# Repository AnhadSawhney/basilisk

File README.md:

# basilisk
 interactive LED art

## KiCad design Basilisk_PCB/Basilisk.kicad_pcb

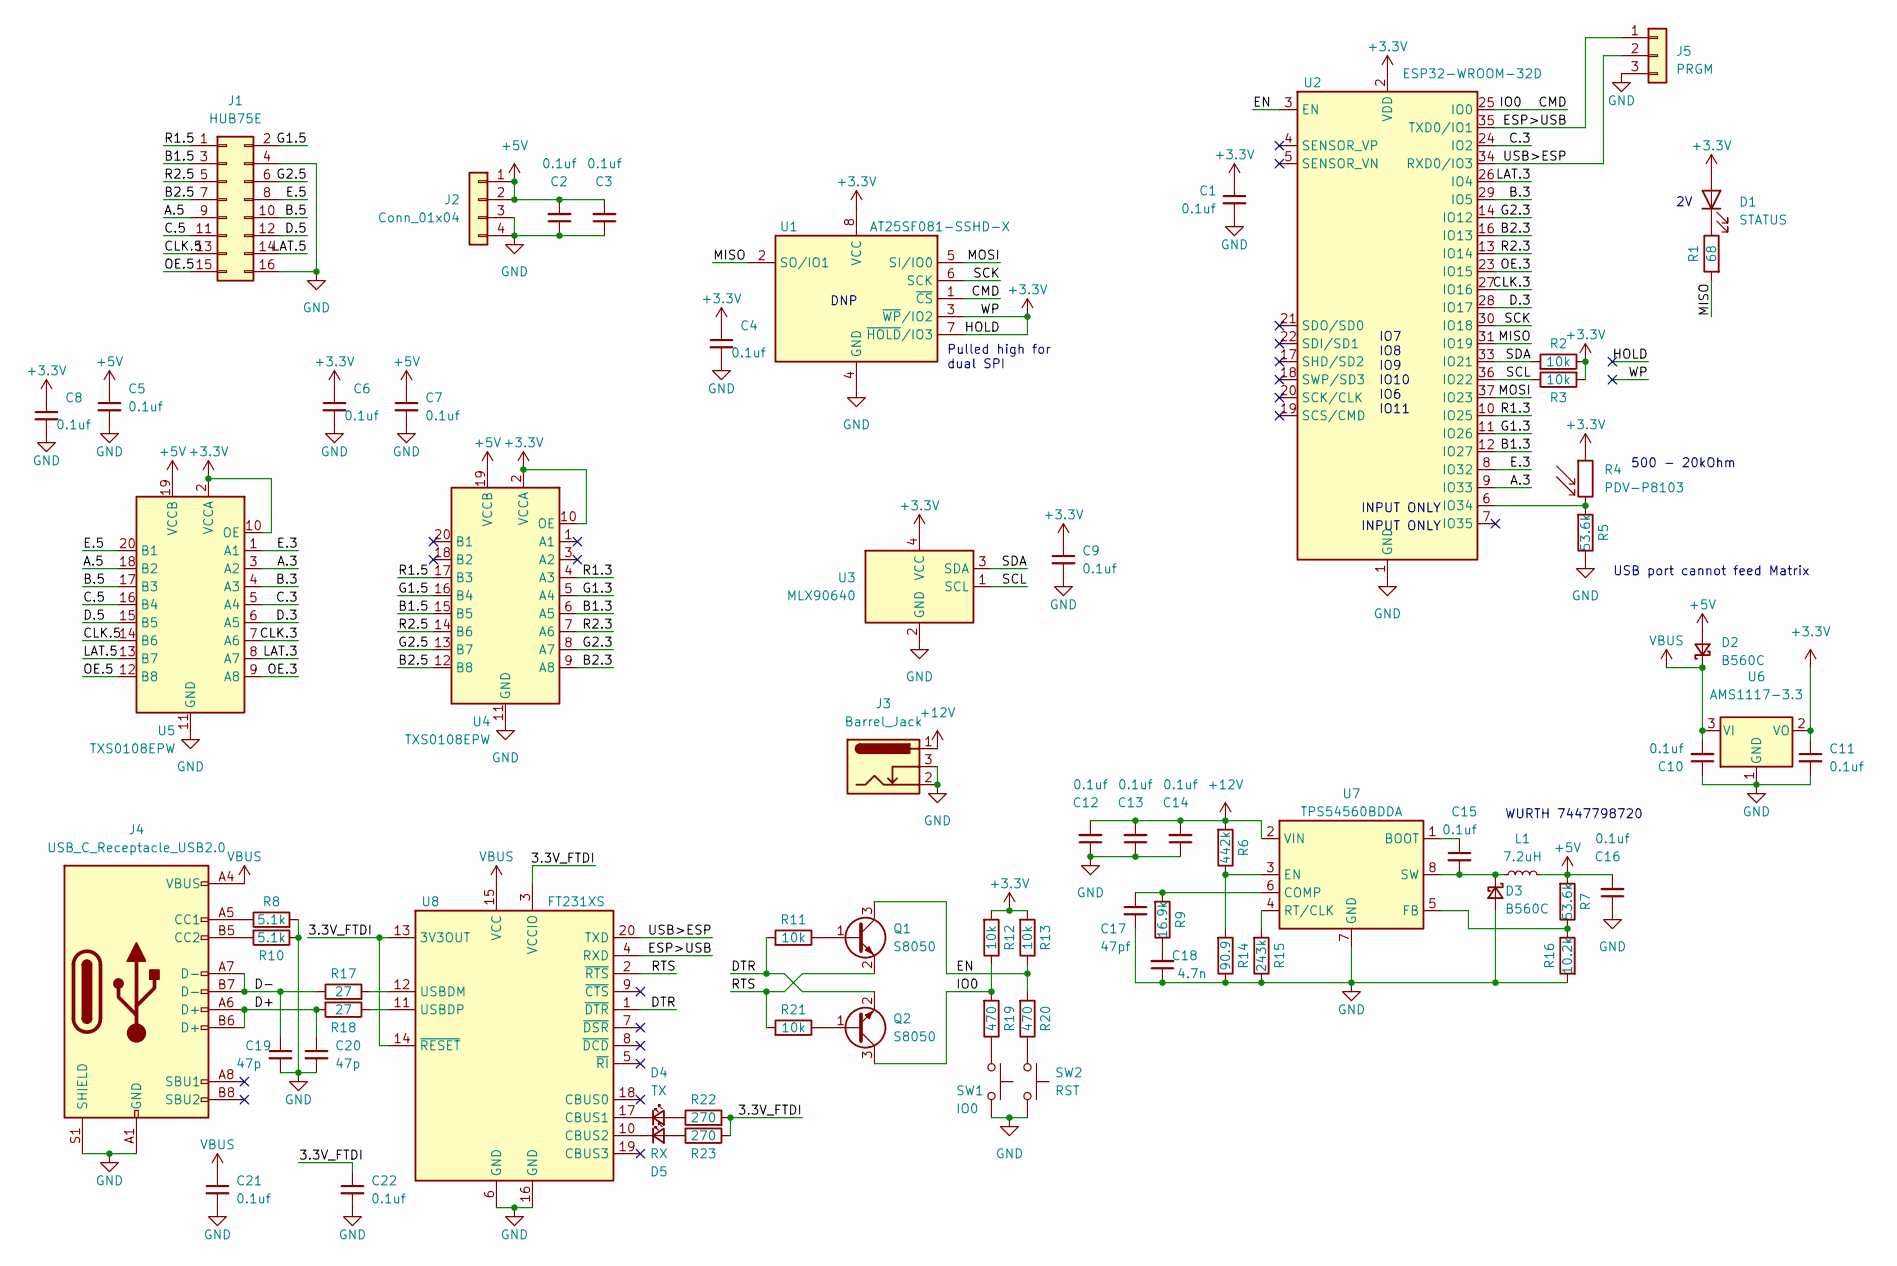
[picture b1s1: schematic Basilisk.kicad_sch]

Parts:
C1, C2, C3, C4, C5, C6, C7, C8, C9, C10, C11, C12, C13, C14, C15, C16, C21, C22: 0.1uf; C_0805_2012Metric
C17: 47pf; C_0805_2012Metric
C18: 4.7n; C_0805_2012Metric
C19, C20: 47p; C_0805_2012Metric
D1: STATUS; LED_D5.0mm_Clear
D2, D3: B560C; D_SMC
D4: TX; LED_0805_2012Metric
D5: RX; LED_0805_2012Metric
J1: HUB75E; PinSocket_2x08_P2.54mm_Vertical
J2: Conn_01x04; Molex_KK-396_A-41791-0004_1x04_P3.96mm_Vertical
J3: Barrel_Jack; BarrelJack_Horizontal
J4: USB_C_Receptacle_USB2.0; USB_C_Receptacle_GCT_USB4085
J5: PRGM; PinHeader_1x03_P2.54mm_Vertical
L1: 7.2uH; L_Wuerth_WE-PDF
Q1, Q2: S8050; SOT-23
R1: 68; R_0805_2012Metric
R2, R3, R11, R12, R13, R21: 10k; R_0805_2012Metric
R4: PDV-P8103; R_LDR_5.0x4.1mm_P3mm_Vertical
R5, R7: 53.6k; R_0805_2012Metric
R6: 442k; R_0805_2012Metric
R8, R10: 5.1k; R_0805_2012Metric
R9: 16.9k; R_0805_2012Metric
R14: 90.9; R_0805_2012Metric
R15: 243k; R_0805_2012Metric
R16: 10.2k; R_0805_2012Metric
R17, R18: 27; R_0805_2012Metric
R19, R20: 470; R_0805_2012Metric
R22, R23: 270; R_0805_2012Metric
SW1: IO0; SW_SPST_EVQP7A
SW2: RST; SW_SPST_EVQP7A
U1: AT25SF081-SSHD-X; SOIC-8_3.9x4.9mm_P1.27mm
U2: ESP32-WROOM-32D; ESP32-WROOM-32
U3: MLX90640; TO292P930H600-4
U4, U5: TXS0108EPW; TSSOP-20_4.4x6.5mm_P0.65mm
U6: AMS1117-3.3; SOT-223-3_TabPin2
U7: TPS54560BDDA; Texas_R-PDSO-G8_EP2.95x4.9mm_Mask2.4x3.1mm_ThermalVias
U8: FT231XS; SSOP-20_3.9x8.7mm_P0.635mm

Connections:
+3.3V: C1.1, C4.1, C6.1, C8.1, C9.1, C11.1, D1.2 (A), R2.1, R3.2, R4.1, R12.2, R13.2, U1.3 (~WP/IO2), U1.7 (~HOLD/IO3), U1.8 (VCC), U2.2 (VDD), U3.4 (VCC), U4.2 (VCCA), U4.10 (OE), U5.2 (VCCA), U5.10 (OE), U6.2 (VO); also elsewhere on the board
+5V: C2.2, C3.2, C5.1, C7.1, C16.2, D2.2 (A), J2.1, J2.2, L1.2, R7.2, U4.19 (VCCB), U5.19 (VCCB)
+12V: C12.2, C13.2, C14.2, J3.1, R6.2, U7.2 (VIN)
/3.3V_FTDI: C22.1, R22.2, R23.1, U8.3 (VCCIO), U8.13 (3V3OUT), U8.14 (~RESET)
/A.3: U2.9 (IO33), U5.3 (A2)
/A.5: J1.9, U5.18 (B2)
/B1.3: U2.12 (IO27), U4.6 (A5)
/B1.5: J1.3, U4.15 (B5)
/B2.3: U2.16 (IO13), U4.9 (A8)
/B2.5: J1.7, U4.12 (B8)
/B.3: U2.29 (IO5), U5.4 (A3)
/B.5: J1.10, U5.17 (B3)
/C.3: U2.24 (IO2), U5.5 (A4)
/C.5: J1.11, U5.16 (B4)
/CLK.3: U2.27 (IO16), U5.7 (A6)
/CLK.5: J1.13, U5.14 (B6)
/CMD: Q2.3 (C), R12.1, R19.2, U1.1 (~CS), U2.25 (IO0)
/D+: C20.1, J4.A6 (D+), J4.B6 (D+), R18.2
/D-: C19.1, J4.A7 (D-), J4.B7 (D-), R17.1
/D.3: U2.28 (IO17), U5.6 (A5)
/D.5: J1.12, U5.15 (B5)
/DTR: Q2.2 (E), R11.2, U8.1 (~DTR)
/E.3: U2.8 (IO32), U5.1 (A1)
/E.5: J1.8, U5.20 (B1)
/EN: Q1.3 (C), R13.1, R20.2, U2.3 (EN)
/ESP>USB: J5.1, U2.35 (TXD0/IO1), U8.4 (RXD)
/G1.3: U2.11 (IO26), U4.5 (A4)
/G1.5: J1.2, U4.16 (B4)
/G2.3: U2.14 (IO12), U4.8 (A7)
/G2.5: J1.6, U4.13 (B7)
/LAT.3: U2.26 (IO4), U5.8 (A7)
/LAT.5: J1.14, U5.13 (B7)
/MISO: R1.2, U1.2 (SO/IO1), U2.31 (IO19)
/MOSI: U1.5 (SI/IO0), U2.37 (IO23)
/OE.3: U2.23 (IO15), U5.9 (A8)
/OE.5: J1.15, U5.12 (B8)
/R1.3: U2.10 (IO25), U4.4 (A3)
/R1.5: J1.1, U4.17 (B3)
/R2.3: U2.13 (IO14), U4.7 (A6)
/R2.5: J1.5, U4.14 (B6)
/RTS: Q1.2 (E), R21.2, U8.2 (~RTS)
/SCK: U1.6 (SCK), U2.30 (IO18)
/SCL: R3.1, U2.36 (IO22), U3.1 (SCL)
/SDA: R2.2, U2.33 (IO21), U3.3 (SDA)
/USB>ESP: J5.2, U2.34 (RXD0/IO3), U8.20 (TXD)
GND: C1.2, C2.1, C3.1, C4.2, C5.2, C6.2, C7.2, C8.2, C9.2, C10.1, C11.2, C12.1, C13.1, C14.1, C16.1, C17.2, C18.1, C19.2, C20.2, C21.2, C22.2, D3.2 (A), J1.4, J1.16, J2.3, J2.4, J3.2, J3.3, J4.A1 (GND), J4.A12 (GND), J4.B1 (GND), J4.B12 (GND), J4.S1 (SHIELD), J5.3, R5.1, R8.2, R10.1, R14.1, R15.1, R16.2, SW1.2, SW2.2, U1.4 (GND), U2.1 (GND), U2.15 (GND), U2.38 (GND), U2.39 (GND), U3.2 (GND), U4.11 (GND), U5.11 (GND), U6.1 (GND), U7.7 (GND), U7.9 (GND), U8.6 (GND), U8.16 (GND)
unnamed: C18.2, R9.1
unnamed: D1.1 (K), R1.1
unnamed: C15.2, D3.1 (K), L1.1, U7.8 (SW)
unnamed: D4.2 (A), R22.1
unnamed: D4.1 (K), U8.17 (CBUS1)
unnamed: D5.2 (A), R23.2
unnamed: D5.1 (K), U8.10 (CBUS2)
unnamed: J4.A5 (CC1), R8.1
unnamed: J4.B5 (CC2), R10.2
unnamed: Q1.1 (B), R11.1
unnamed: Q2.1 (B), R21.1
unnamed: R19.1, SW1.1
unnamed: R20.1, SW2.1
unnamed 59: R4.2, R5.2, U2.6 (IO34); also elsewhere on the board
unnamed: C15.1, U7.1 (BOOT)
unnamed: C17.1, R9.2, U7.6 (COMP)
unnamed: R6.1, R14.2, U7.3 (EN)
unnamed: R7.1, R16.1, U7.5 (FB)
unnamed: R15.2, U7.4 (RT/CLK)
unnamed: R17.2, U8.12 (USBDM)
unnamed: R18.1, U8.11 (USBDP)
VBUS: C10.2, C21.1, D2.1 (K), J4.A4 (VBUS), J4.A9 (VBUS), J4.B4 (VBUS), J4.B9 (VBUS), U6.3 (VI), U8.15 (VCC)

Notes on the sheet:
DNP
USB port cannot feed Matrix
WURTH 7447798720
500 - 20kOhm
IO7 IO8 IO9 IO10 IO6 IO11
Pulled high for dual SPI
INPUT ONLY

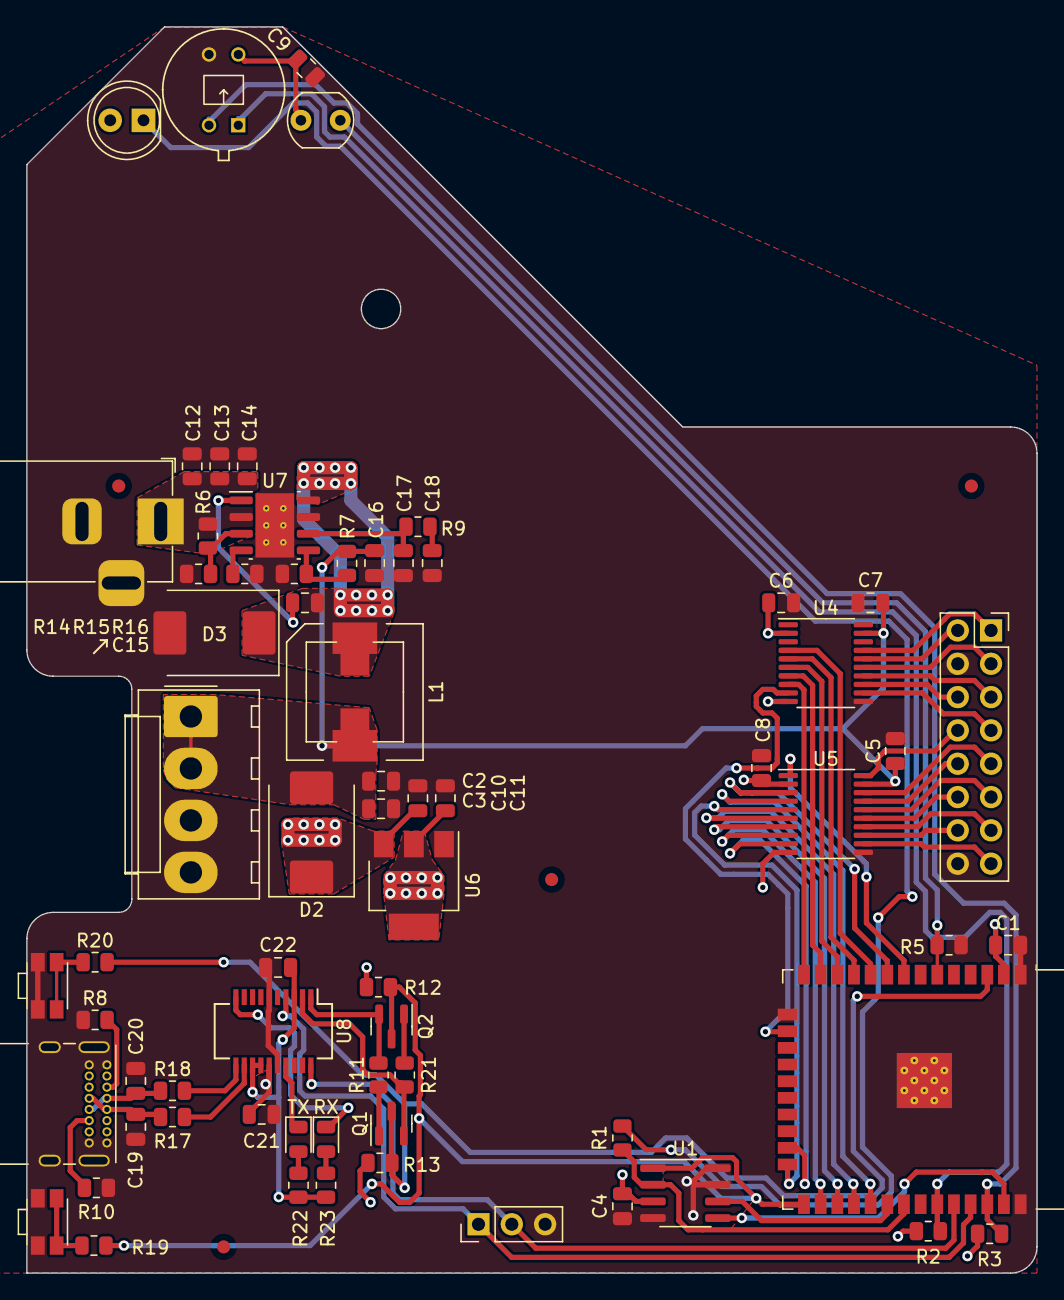
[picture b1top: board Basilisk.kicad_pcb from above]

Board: 2 copper layers, 77.0 x 95.0 mm, 68 parts (0 on the bottom side), 68 nets.

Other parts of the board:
Ree: PDV-P8103; R_LDR_5.0x4.1mm_P3mm_Vertical

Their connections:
+3.3V: Ree.1; also elsewhere on the board
unnamed 59: Ree.2; also elsewhere on the board

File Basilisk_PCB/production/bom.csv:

Designator,Footprint,Quantity,Value,LCSC Part #
C1,0805,1,0.1uf,
C10,0805,1,0.1uf,
C11,0805,1,0.1uf,
C12,0805,1,0.1uf,
C13,0805,1,0.1uf,
C14,0805,1,0.1uf,
C15,0805,1,0.1uf,
C16,0805,1,0.1uf,
C17,0805,1,47pf,
C18,0805,1,4.7n,
C19,0805,1,47p,
C2,0805,1,0.1uf,
C20,0805,1,47p,
C21,0805,1,0.1uf,
C22,0805,1,0.1uf,
C3,0805,1,0.1uf,
C4,0805,1,0.1uf,
C5,0805,1,0.1uf,
C6,0805,1,0.1uf,
C7,0805,1,0.1uf,
C8,0805,1,0.1uf,
C9,0805,1,0.1uf,
D1,LED_D5.0mm_Clear,1,STATUS,
"D2, D3",D_SMC,2,B560C,
D4,0805,1,TX,
D5,0805,1,RX,
J1,PinSocket_2x08_P2.54mm_Vertical,1,HUB75E,
J2,Molex_KK-396_A-41791-0004_1x04_P3.96mm_Vertical,1,Conn_01x04,
J3,BarrelJack_Horizontal,1,Barrel_Jack,
J4,USB_C_Receptacle_GCT_USB4085,1,USB_C_Receptacle_USB2.0,
J5,PinHeader_1x03_P2.54mm_Vertical,1,PRGM,
L1,L_Wuerth_WE-PDF,1,7.2uH,
"Q1, Q2",SOT-23,2,S8050,
R1,0805,1,68,
R10,0805,1,5.1k,
R11,0805,1,10k,
R12,0805,1,10k,
R13,0805,1,10k,
R14,0805,1,90.9,
R15,0805,1,243k,
R16,0805,1,10.2k,
R17,0805,1,27,
R18,0805,1,27,
R19,0805,1,470,
R2,0805,1,10k,
R20,0805,1,470,
R21,0805,1,10k,
R22,0805,1,270,
R23,0805,1,270,
R3,0805,1,10k,
R4,R_LDR_5.0x4.1mm_P3mm_Vertical,1,PDV-P8103,
R5,0805,1,53.6k,
R6,0805,1,442k,
R7,0805,1,53.6k,
R8,0805,1,5.1k,
R9,0805,1,16.9k,
SW1,SW_SPST_EVQP7A,1,IO0,
SW2,SW_SPST_EVQP7A,1,RST,
U1,SOIC-8_3.9x4.9mm_P1.27mm,1,AT25SF081-SSHD-X,
U2,ESP32-WROOM-32,1,ESP32-WROOM-32D,
U3,TO292P930H600-4,1,MLX90640,
"U4, U5",TSSOP-20_4.4x6.5mm_P0.65mm,2,TXS0108EPW,
U6,SOT-223-3_TabPin2,1,AMS1117-3.3,
U7,Texas_R-PDSO-G8_EP2.95x4.9mm_Mask2.4x3.1mm_ThermalVias,1,TPS54560BDDA,
U8,SSOP-20_3.9x8.7mm_P0.635mm,1,FT231XS,

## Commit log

2022-10-31 upload KiCAD files
2022-10-31 upload concept art
2022-10-31 finish schematic?
2022-10-31 get firmware setup
2022-11-02 read thermal camera
2022-11-02 first prototype: thermal matrix cam
2022-11-14 upload pictures
2022-11-14 remove redundant files
2022-11-16 start python code
2022-11-16 added "hello anhad"
2022-11-16 add todos
2022-11-23 add CAD model of matrix
2022-12-18 blinking skin
2023-02-06 set up fixed components on board
2023-03-06 Routed PCB
    Routed most of PCB
2023-03-06 almost done routuing
2023-03-11 version 1.0
2023-03-12 start solidworks cad
2023-03-14 start frame CAD
2023-03-15 more progress on frame
2023-03-23 blinking and looking at mouse
2023-03-23 eye backgrounds
2023-03-23 converting to images to array
2023-03-27 image arrays
2023-03-27 warp the eye
2023-03-27 start blending backgrounds
2023-04-04 working on actual hardware
2023-04-05 pincushion distortion test
2023-04-09 minimum viable product
